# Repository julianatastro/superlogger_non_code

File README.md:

# superlogger_non_code
For PCBs and 3d-models

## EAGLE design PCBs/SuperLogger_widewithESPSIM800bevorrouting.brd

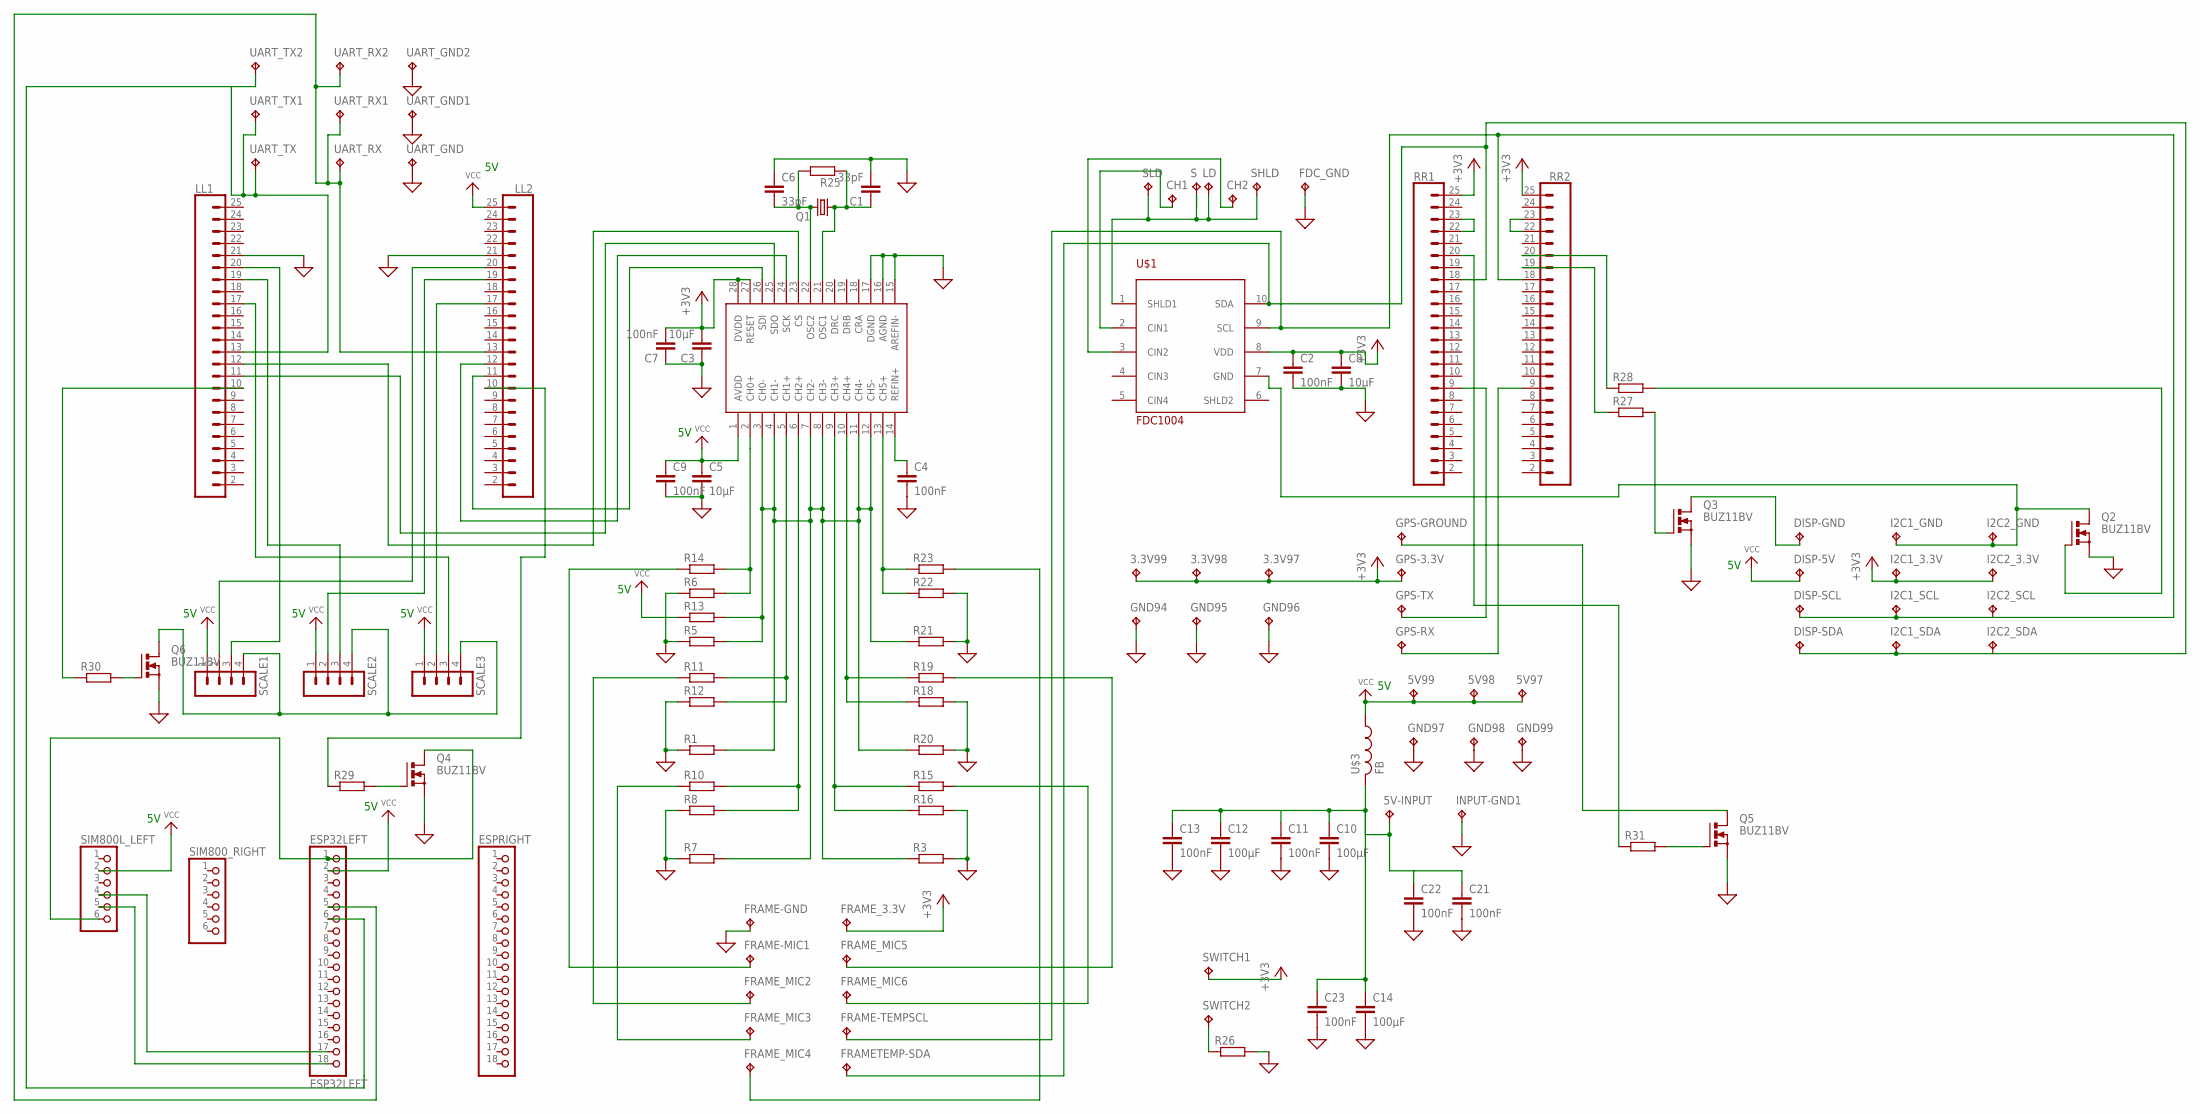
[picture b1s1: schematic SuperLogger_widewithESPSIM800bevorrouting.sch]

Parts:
3.3V97, 3.3V98, 3.3V99, 5V97, 5V98, 5V99, 5V-INPUT: ground; P1-13Y
C1, C6: 33pF; C5B3
C2, C4, C7, C9, C11, C13, C21, C22, C23: 100nF; C5B3
C3, C5, C8: 10µF; C5B3
C10, C12, C14: 100µF; C5B3
CH1, CH2: ground; P1-13Y
DISP-5V: ground; P1-13Y
DISP-GND: ground; P1-13Y
DISP-SCL: ground; P1-13Y
DISP-SDA: ground; P1-13Y
ESP32LEFT: ESP32LEFT; 1X18-BIG
ESPRIGHT: PINHD-1X18-BIG; 1X18-BIG
FDC_GND: ground; P1-13Y
FRAME-GND: ground; P1-13Y
FRAME-MIC1: ground; P1-13Y
FRAME-TEMPSCL: ground; P1-13Y
FRAMETEMP-SDA: ground; P1-13Y
FRAME_3.3V: ground; P1-13Y
FRAME_MIC2, FRAME_MIC3, FRAME_MIC4, FRAME_MIC5, FRAME_MIC6: ground; P1-13Y
GND94, GND95, GND96, GND97, GND98, GND99: ground; P1-13Y
GPS-3.3V: ground; P1-13Y
GPS-GROUND: ground; P1-13Y
GPS-RX: ground; P1-13Y
GPS-TX: ground; P1-13Y
I2C1_3.3V, I2C1_GND, I2C1_SCL, I2C1_SDA, I2C2_3.3V, I2C2_GND, I2C2_SCL, I2C2_SDA: ground; P1-13Y
INPUT-GND1: ground; P1-13Y
LD: ground; P1-13Y
LL1, LL2: CONN_24; 1X24
Q1: CRYSTALHC49S; HC49/S
Q2, Q3, Q4, Q5, Q6: BUZ11BV; TO220BV
R1, R3, R5, R6, R7, R8, R10, R11, R12, R13, R14, R15, R16, R18, R19, R20, R21, R22, R23, R25, R26, R27, R28, R29, R30, R31: R0207/10; 0207/10
RR1, RR2: CONN_24; 1X24
S: ground; P1-13Y
SCALE1, SCALE2, SCALE3: MA04-1
SHLD: ground; P1-13Y
SIM800L_LEFT, SIM800_RIGHT: PINHD-1X6; 1X06
SLD: ground; P1-13Y
SWITCH1, SWITCH2: ground; P1-13Y
U$1: FDC1004; MSOP10
U$2: MCP3903; MSOP8_0.65MM
U$3: FB
UART_GND, UART_GND1, UART_GND2: ground; P1-13Y
UART_RX, UART_RX1, UART_RX2: ground; P1-13Y
UART_TX, UART_TX1, UART_TX2: ground; P1-13Y

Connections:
+3V3: 3.3V97.TP, 3.3V98.TP, 3.3V99.TP, C2.1, C3.2, C7.2, C8.1, FRAME_3.3V.TP, GPS-3.3V.TP, I2C1_3.3V.TP, I2C2_3.3V.TP, RR1.25, RR2.25, SWITCH1.TP, U$1.8 (VDD), U$2.27 (RESET), U$2.28 (DVDD)
GND: C1.2, C2.2, C3.1, C4.2, C5.2, C6.1, C7.1, C8.2, C9.2, C10.2, C11.2, C12.2, C13.2, C14.2, C21.2, C22.2, C23.2, FDC_GND.TP, FRAME-GND.TP, GND94.TP, GND95.TP, GND96.TP, GND97.TP, GND98.TP, GND99.TP, INPUT-GND1.TP, LL1.21, LL2.21, Q2.S, Q3.S, Q4.S, Q5.S, Q6.S, R1.1, R3.2, R5.1, R6.1, R7.1, R8.1, R12.1, R16.2, R18.2, R20.2, R21.2, R22.2, R26.2, U$2.15 (AREFIN-), U$2.16 (AGND), U$2.17 (DGND), UART_GND.TP, UART_GND1.TP, UART_GND2.TP
unnamed: ESP32LEFT.6, LL1.13, UART_TX.TP, UART_TX1.TP, UART_TX2.TP
unnamed: R15.1, R16.1, U$2.9 (CH3+)
unnamed: DISP-SDA.TP, FRAMETEMP-SDA.TP, I2C1_SDA.TP, I2C2_SDA.TP, RR1.18, U$1.10 (SDA)
unnamed: R26.1, SWITCH2.TP
unnamed: FRAME_MIC3.TP, R10.1
unnamed: LL2.17, SCALE3.2
unnamed: LD.TP, S.TP, SHLD.TP, SLD.TP, U$1.1 (SHLD1)
unnamed: DISP-SCL.TP, FRAME-TEMPSCL.TP, I2C1_SCL.TP, I2C2_SCL.TP, RR2.18, U$1.9 (SCL)
unnamed: CH1.TP, U$1.2 (CIN1)
unnamed: ESP32LEFT.5, LL2.13, UART_RX.TP, UART_RX1.TP, UART_RX2.TP
unnamed: I2C1_GND.TP, I2C2_GND.TP, Q2.D, U$1.7 (GND)
unnamed: LL2.19, SCALE2.2
unnamed: Q2.G, R28.2
unnamed: LL2.20, SCALE1.2
unnamed: LL1.19, SCALE2.3
unnamed: LL1.20, SCALE1.3
unnamed: R22.1, R23.1, U$2.13 (CH5+)
unnamed: C6.2, Q1.2, R25.2, U$2.22 (OSC2)
unnamed: C1.1, Q1.1, R25.1, U$2.21 (OSC1)
unnamed: LL1.12, U$2.23 (CS)
unnamed: LL2.12, U$2.24 (SCK)
unnamed: FRAME-MIC1.TP, R14.1
unnamed: FRAME_MIC2.TP, R11.1
unnamed: ESP32LEFT.18, SIM800L_LEFT.5
unnamed: R8.2, R10.2, U$2.6 (CH2+)
unnamed: R11.2, R12.2, U$2.5 (CH1+)
unnamed: FRAME_MIC6.TP, R15.2
unnamed: RR2.22, RR2.23
unnamed: R1.2, R3.1, R5.2, R7.2, R13.2, R20.1, R21.1, U$2.3 (CH0-), U$2.4 (CH1-), U$2.7 (CH2-), U$2.8 (CH3-), U$2.11 (CH4-), U$2.12 (CH5-)
unnamed: R6.2, R14.2, U$2.2 (CH0+)
unnamed: R18.1, R19.1, U$2.10 (CH4+)
unnamed: LL1.11, U$2.25 (SDO)
unnamed: ESP32LEFT.17, SIM800L_LEFT.4
unnamed: Q4.G, R29.2
unnamed: FRAME_MIC4.TP, R23.2
unnamed: LL2.11, U$2.26 (SDI)
unnamed: GPS-RX.TP, RR2.9
unnamed: Q6.D, SCALE1.4, SCALE2.4, SCALE3.4
unnamed: CH2.TP, U$1.3 (CIN2)
unnamed: GPS-TX.TP, RR1.9
unnamed: RR1.22, RR1.23
unnamed: Q3.G, R27.2
unnamed: ESP32LEFT.1, Q4.D, SIM800L_LEFT.6
unnamed: DISP-GND.TP, Q3.D
unnamed: R31.1, RR1.20
unnamed: GPS-GROUND.TP, Q5.D
unnamed: FRAME_MIC5.TP, R19.2
unnamed: Q6.G, R30.2
unnamed: Q5.G, R31.2
unnamed: R28.1, RR2.20
unnamed: C4.1, U$2.14 (REFIN+)
unnamed: R27.1, RR2.19
unnamed: LL1.17, SCALE3.3
unnamed: LL1.10, R30.1
unnamed: LL2.10, R29.1
VCC: 5V97.TP, 5V98.TP, 5V99.TP, 5V-INPUT.TP, C5.1, C9.1, C10.1, C11.1, C12.1, C13.1, C14.1, C21.1, C22.1, C23.1, DISP-5V.TP, ESP32LEFT.2, LL2.25, R13.1, SCALE1.1, SCALE2.1, SCALE3.1, SIM800L_LEFT.2, U$2.1 (AVDD), U$3.P$1 (1), U$3.P$2 (2)

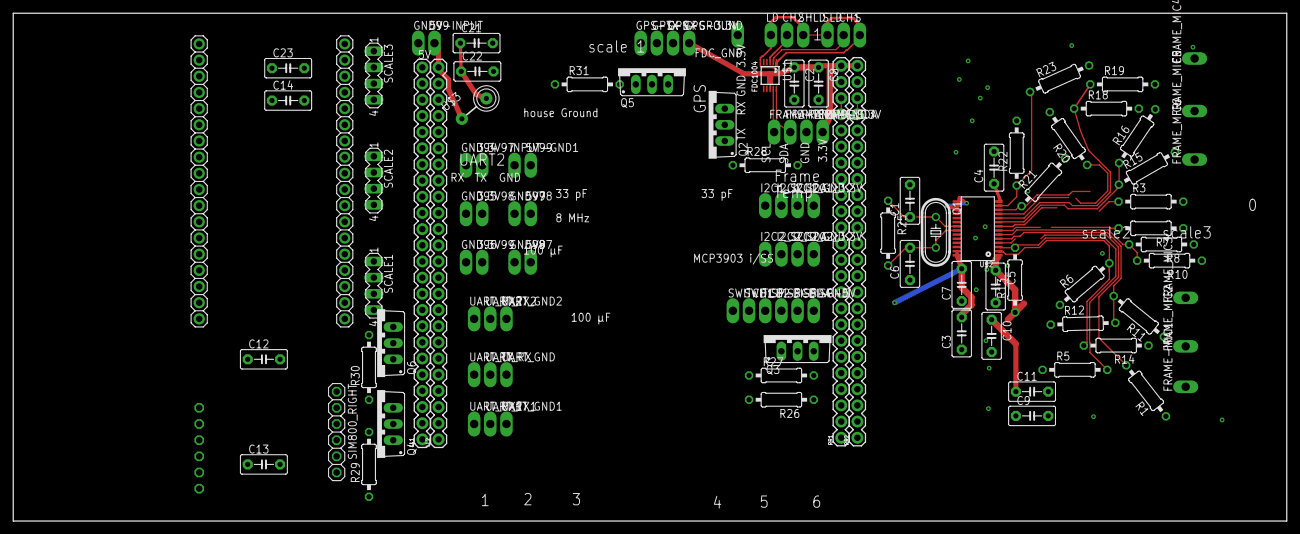
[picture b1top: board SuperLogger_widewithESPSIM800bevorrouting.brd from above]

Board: 2 copper layers, 200.0 x 79.8 mm, 121 parts (1 on the bottom side), 58 nets.

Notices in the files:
parts and their libraries:
SparkFun-Connectors: Licensing: Creative Commons ShareAlike 4.0 International - https://creativecommons.org/licenses/by-sa/4.0
